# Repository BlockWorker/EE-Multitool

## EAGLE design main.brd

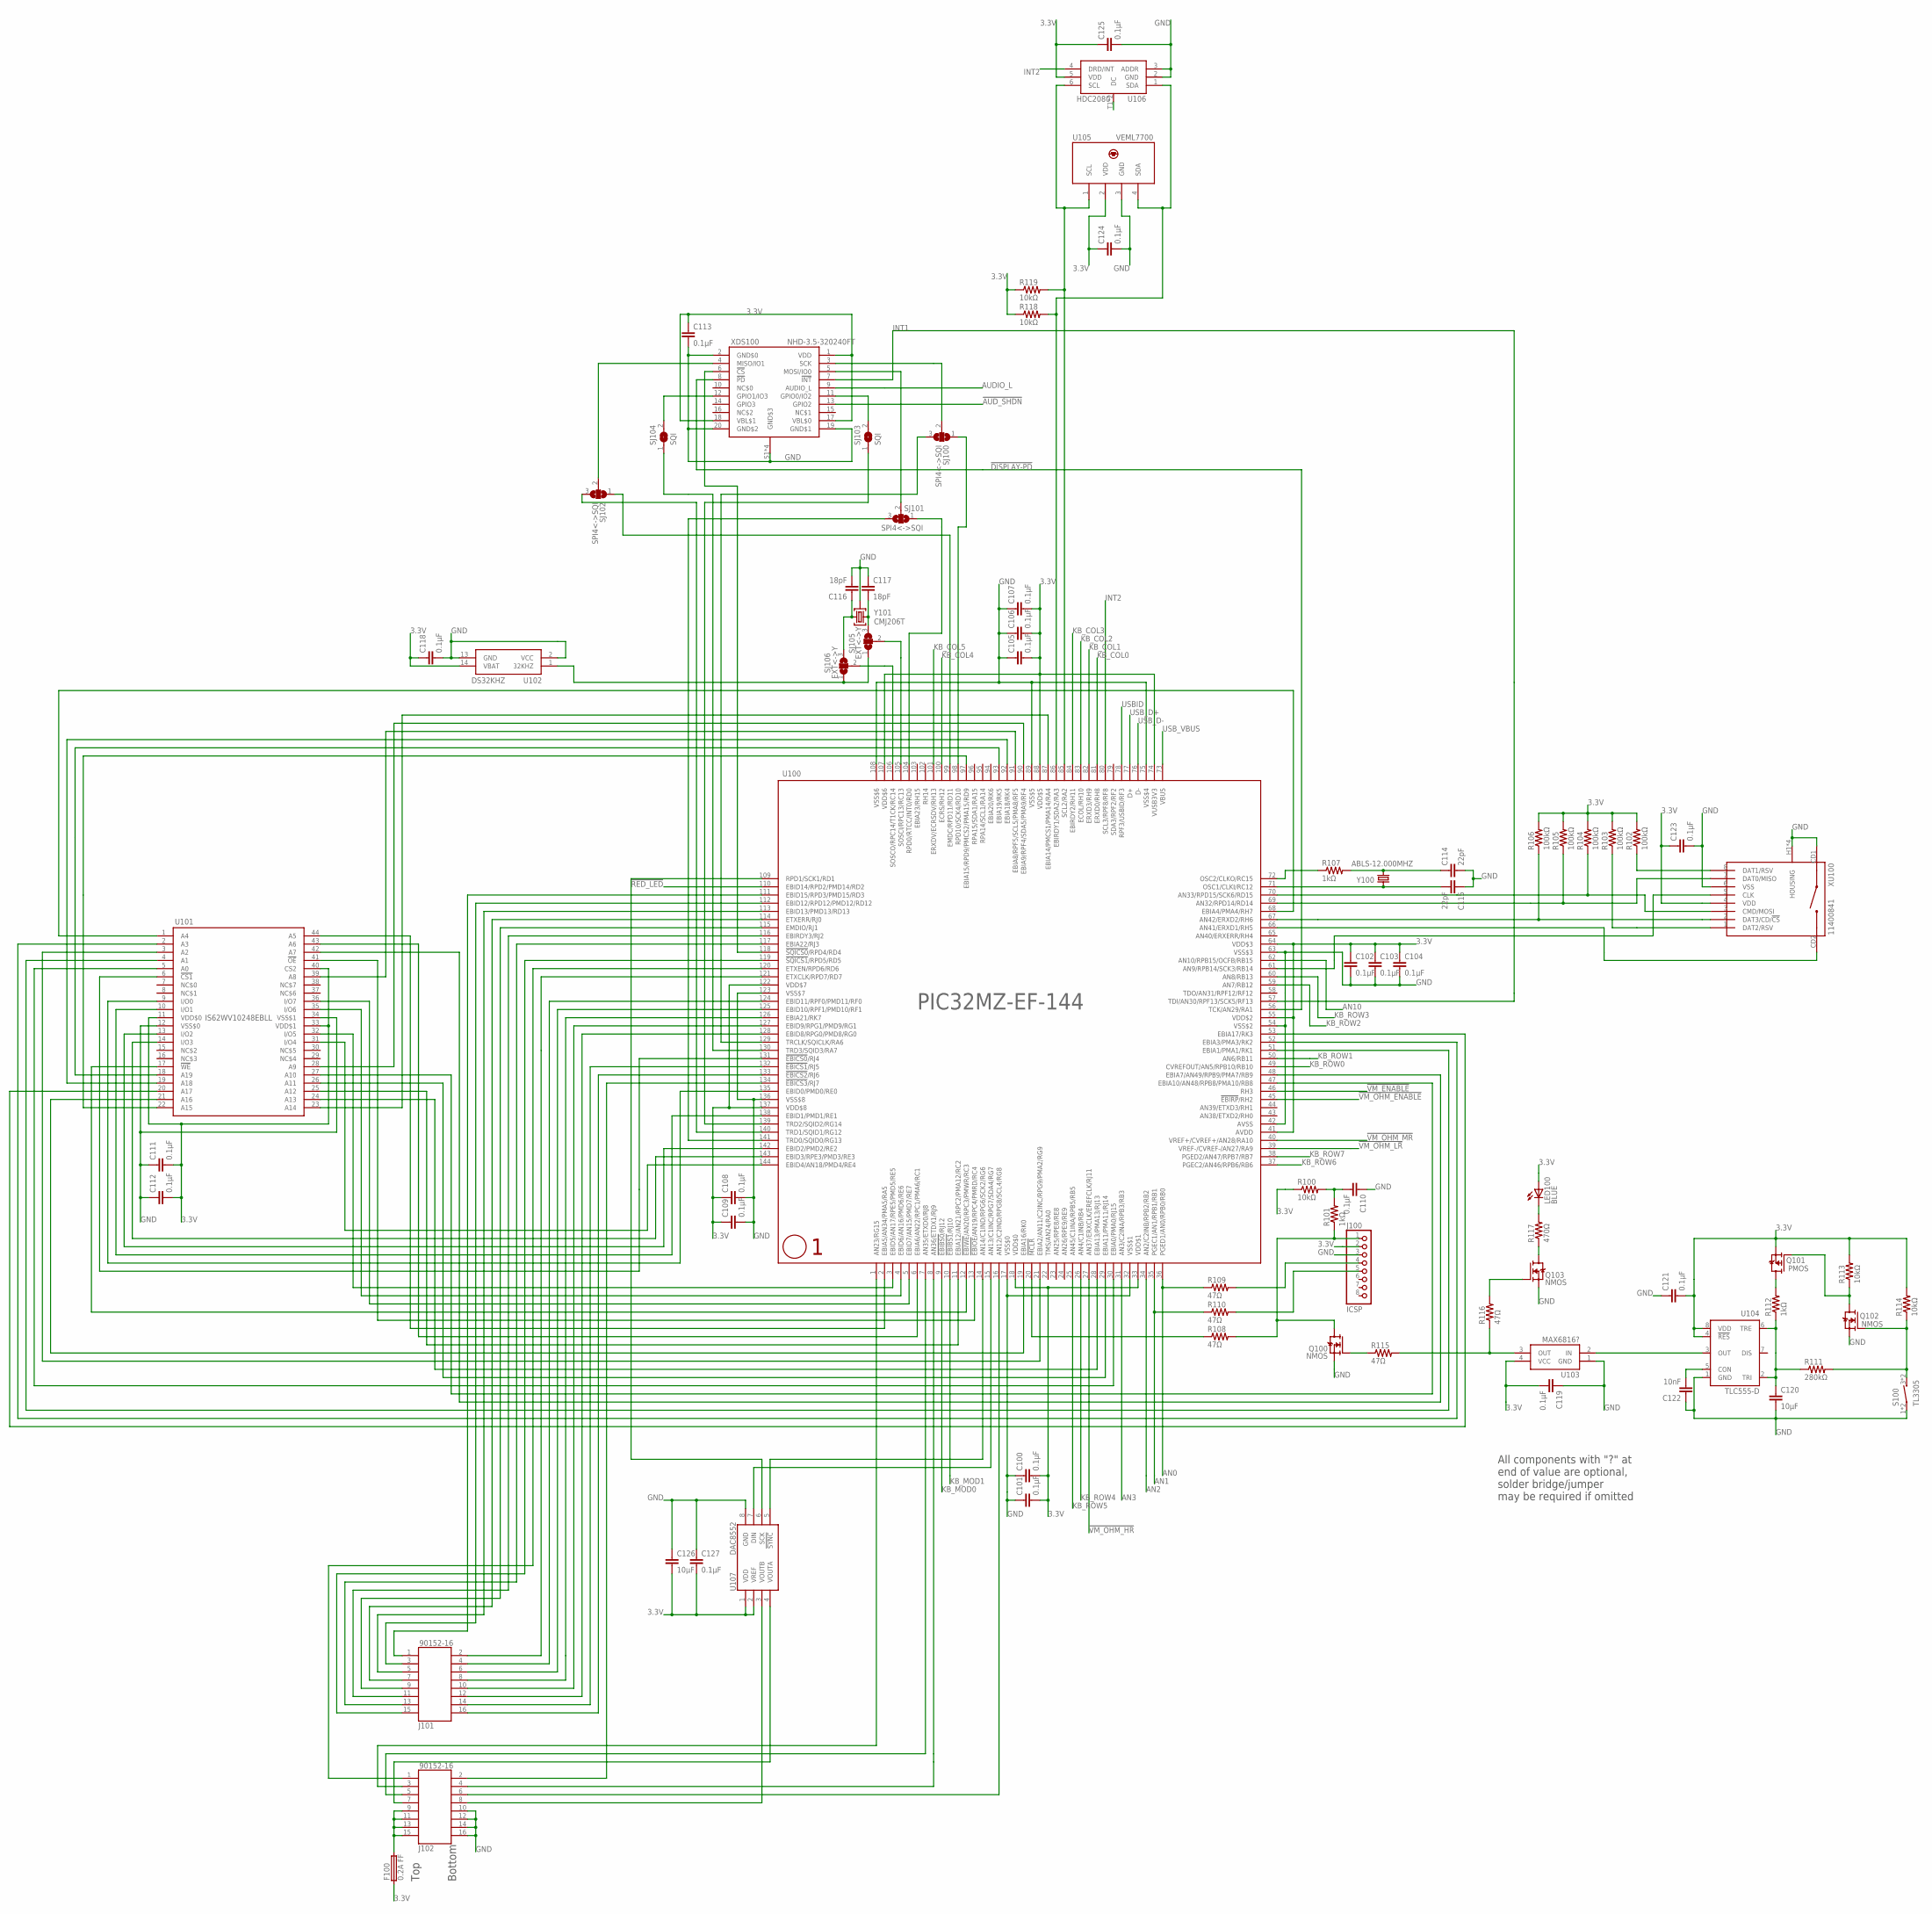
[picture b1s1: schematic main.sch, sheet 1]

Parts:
C100, C101, C102, C103, C104, C105, C106, C107, C108, C109, C110, C111, C112, C113, C118, C119, C121, C123, C124, C125, C127: 0.1µF; C0805K
C114, C115: 22pF; C0805K
C116, C117: 18pF; C0805K
C120, C126: 10µF; C0805K
C122: 10nF; C0805K
F100: 0.2A FF; C1206K
J100: ICSP; 1X08
J101, J102: 90152-16
LED100: BLUE; CHIP-LED0805
Q100, Q102, Q103: NMOS; SOT23
Q101: PMOS; SOT23
R100, R113, R114, R118, R119: 10kΩ; R0805
R101, R107, R112: 1kΩ; R0805
R102, R103, R104, R105, R106: 100kΩ; R0805
R108, R109, R110, R115, R116: 47Ω; R0805
R111: 280kΩ; R0805
R117: 470Ω; R0805
S100: TL3305; TL3305_MICROSWITCH
SJ100, SJ101, SJ102: SPI4<->SQI; SJ_2
SJ103, SJ104: SQI; SJ
SJ105, SJ106: EXT<->Y; SJ_2
U100: PIC32MZ-EF-144; LQFP144-20X20
U101: IS62WV10248EBLL; TSOP44
U102: DS32KHZ; SO16L
U103: MAX6816?; SOT143
U104: TLC555-D; SOIC8
U105: VEML7700
U106: HDC2080; PWSON-6
U107: DAC8552; MSOP8
XDS100: NHD-3.5-320240FT; NHD_DISPLAY_CONN
XU100: 11400841
Y100: ABLS-12.000MHZ; HC49US
Y101: CMJ206T; CMJ206T-CUSTOM

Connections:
3.3V: C100.2, C101.2, C102.1, C103.1, C104.1, C105.2, C106.2, C107.2, C108.1, C109.1, C111.2, C112.2, C113.1, C118.1, C119.2, C121.2, C123.1, C124.1, C125.1, C126.2, C127.2, F100.1, J100.2, LED100.A, Q101.2 (S), R100.1, R102.2, R103.2, R104.2, R105.2, R106.2, R113.2, R114.2, R118.1, R119.1, U100.18 (VDD$0), U100.33 (VDD$1), U100.41 (AVDD), U100.55 (VDD$2), U100.64 (VDD$3), U100.74 (VUSB3V3), U100.88 (VDD$5), U100.107 (VDD$6), U100.122 (VDD$7), U100.137 (VDD$8), U101.11 (VDD$0), U101.33 (VDD$1), U101.40 (CS2), U102.14 (VBAT), U103.4 (VCC), U104.4 (!RES), U104.8 (VDD), U105.2 (VDD), U106.5 (VDD), U107.1 (VDD), U107.2 (VREF), XDS100.1 (VDD), XDS100.17 (VBL$0), XDS100.18 (VBL$1), XU100.4 (VDD); also elsewhere on the board
!AUD_SHDN: XDS100.13 (GPIO2); also elsewhere on the board
!DISPLAY-PD: U100.56 (TCK/AN29/RA1), XDS100.8 (!PD)
!EBICS0: U100.131 (!EBICS0!/RJ4), U101.6 (!CS1)
!EBIOE: U100.13 (!EBIOE!/AN19/RPC4/PMRD/RC4), U101.41 (!OE)
!EBIWE: U100.12 (!EBIWE!/AN20/RPC3/PMWR/RC3), U101.17 (!WE)
!MCLR: R108.1, U100.20 (!MCLR)
!MCLR!_FILTER: C110.2, R100.2, R101.2
!MCLR!_R: J100.1, Q100.3 (D), R101.1, R108.2
!RED_LED: U100.110 (EBID14/RPD2/PMD14/RD2); also elsewhere on the board
!RESET_MAN!_RAW: Q102.1 (G), R111.2, R114.1, S100.3 (2), S100.4 (2)
!SQICS0: U100.118 (!SQICS0!/RPD4/RD4), XDS100.6 (!CS)
!VM_ENABLE: U100.46 (RH3); also elsewhere on the board
!VM_OHM_ENABLE: U100.45 (!EBIRP!/RH2); also elsewhere on the board
!VM_OHM_HR: U100.27 (AN37/ERXCLK/EREFCLK/RJ11); also elsewhere on the board
!VM_OHM_LR: U100.39 (VREF-/CVREF-/AN27/RA9); also elsewhere on the board
!VM_OHM_MR: U100.40 (VREF+/CVREF+/AN28/RA10); also elsewhere on the board
AN0: R109.1, U100.36 (PGED1/AN0/RPB0/RB0); also elsewhere on the board
AN1: R110.1, U100.35 (PGEC1/AN1/RPB1/RB1); also elsewhere on the board
AN2: U100.34 (AN2/C2INB/RPB2/RB2); also elsewhere on the board
AN3: U100.31 (AN3/C2INA/RPB3/RB3); also elsewhere on the board
AN10: U100.62 (AN10/RPB15/OCFB/RB15); also elsewhere on the board
AN12/A3: J102.6, U100.16 (AN12/C2IND/RPG8/SCL4/RG8)
AN23/A0: J102.3, U100.1 (AN23/RG15)
AN35/A1: J102.5, U100.7 (AN35/ETXD0/RJ8)
AN36/A2: J102.4, U100.8 (AN36/ETDX1/RJ9)
AUDIO_L: XDS100.9 (AUDIO_L); also elsewhere on the board
DAC_OUT_A: J102.7, U107.4 (VOUTA)
DAC_OUT_B: J102.8, U107.3 (VOUTB)
DISP_IO0: SJ101.2, XDS100.5 (MOSI/IO0)
DISP_IO1: SJ102.2, XDS100.4 (MISO/IO1)
DISP_IO2: SJ103.2, XDS100.11 (GPIO0/IO2)
DISP_IO3: SJ104.2, XDS100.12 (GPIO1/IO3)
DISP_SCK: SJ100.2, XDS100.3 (SCK)
EBIA0: U100.30 (EBIA0/PMA0/RJ15), U101.5 (A0)
EBIA1: U100.51 (EBIA1/PMA1/RK1), U101.4 (A1)
EBIA2: U100.21 (EBIA2/AN11/C2INC/RPG9/PMA2/RG9), U101.3 (A2)
EBIA3: U100.52 (EBIA3/PMA3/RK2), U101.2 (A3)
EBIA4: U100.68 (EBIA4/PMA4/RH7), U101.1 (A4)
EBIA5: U100.2 (EBIA5/AN34/PMA5/RA5), U101.44 (A5)
EBIA6: U100.6 (EBIA6/AN22/RPC1/PMA6/RC1), U101.43 (A6)
EBIA7: U100.48 (EBIA7/AN49/RPB9/PMA7/RB9), U101.42 (A7)
EBIA8: U100.91 (EBIA8/RPF5/SCL5/PMA8/RF5), U101.39 (A8)
EBIA9: U100.90 (EBIA9/RPF4/SDA5/PMA9/RF4), U101.28 (A9)
EBIA10: U100.47 (EBIA10/AN48/RPB8/PMA10/RB8), U101.27 (A10)
EBIA11: U100.29 (EBIA11/PMA11/RJ14), U101.26 (A11)
EBIA12: U100.11 (EBIA12/AN21/RPC2/PMA12/RC2), U101.25 (A12)
EBIA13: U100.28 (EBIA13/PMA13/RJ13), U101.24 (A13)
EBIA14: U100.87 (EBIA14/PMCS1/PMA14/RA4), U101.23 (A14)
EBIA15: U100.97 (EBIA15/RPD9/PMCS2/PMA15/RD9), U101.22 (A15)
EBIA16: U100.19 (EBIA16/RK0), U101.21 (A16)
EBIA17: U100.53 (EBIA17/RK3), U101.20 (A17)
EBIA18: U100.92 (EBIA18/RK4), U101.19 (A18)
EBIA19: U100.93 (EBIA19/RK5), U101.18 (A19)
EBID0: U100.135 (EBID0/PMD0/RE0), U101.9 (I/O0)
EBID1: U100.138 (EBID1/PMD1/RE1), U101.10 (I/O1)
EBID2: U100.142 (EBID2/PMD2/RE2), U101.13 (I/O2)
EBID3: U100.143 (EBID3/RPE3/PMD3/RE3), U101.14 (I/O3)
EBID4: U100.144 (EBID4/AN18/PMD4/RE4), U101.31 (I/O4)
EBID5: U100.3 (EBID5/AN17/RPE5/PMD5/RE5), U101.32 (I/O5)
EBID6: U100.4 (EBID6/AN16/PMD6/RE6), U101.35 (I/O6)
EBID7: U100.5 (EBID7/AN15/PMD7/RE7), U101.36 (I/O7)
GND: C100.1, C101.1, C102.2, C103.2, C104.2, C105.1, C106.1, C107.1, C108.2, C109.2, C110.1, C111.1, C112.1, C113.2, C114.2, C115.1, C116.2, C117.1, C118.2, C119.1, C120.2, C121.1, C122.1, C123.2, C124.2, C125.2, C126.1, C127.1, J100.3, J102.10, J102.12, J102.14, J102.16, Q100.2 (S), Q102.2 (S), Q103.2 (S), S100.1, S100.2 (1), U100.17 (VSS$0), U100.32 (VSS$1), U100.42 (AVSS), U100.54 (VSS$2), U100.63 (VSS$3), U100.75 (VSS$4), U100.89 (VSS$5), U100.108 (VSS$6), U100.123 (VSS$7), U100.136 (VSS$8), U101.12 (VSS$0), U101.34 (VSS$1), U102.2 (VCC), U102.13 (GND), U103.1 (GND), U104.1 (GND), U105.3 (GND), U106.2 (GND), U106.3 (ADDR), U107.8 (GND), XDS100.2 (GND$0), XDS100.19 (GND$1), XDS100.20 (GND$2), XDS100.S1 (GND$3), XDS100.S2 (GND$3), XDS100.S3 (GND$3), XDS100.S4 (GND$3), XU100.6 (VSS), XU100.CD1, XU100.H1 (HOUSING), XU100.H2 (HOUSING), XU100.H3 (HOUSING), XU100.H4 (HOUSING), Y101.GND (3); also elsewhere on the board
INT1: U100.57 (TDI/AN30/RPF13/SCK5/RF13), XDS100.7 (!INT)
INT2: U100.80 (SCL3/RPF8/RF8), U106.4 (DRD/INT)
KB_COL0: U100.81 (ERXD0/RH8); also elsewhere on the board
KB_COL1: U100.82 (ERXD3/RH9); also elsewhere on the board
KB_COL2: U100.83 (ECOL/RH10); also elsewhere on the board
KB_COL3: U100.84 (EBIRDY2/RH11); also elsewhere on the board
KB_COL4: U100.100 (ECRS/RH12); also elsewhere on the board
KB_COL5: U100.101 (ERXDV/ECRSDV/RH13); also elsewhere on the board
KB_MOD0: U100.9 (!EBIBS0!/RJ12); also elsewhere on the board
KB_MOD1: U100.10 (!EBIBS1!/RJ10); also elsewhere on the board
KB_ROW0: U100.49 (CVREFOUT/AN5/RPB10/RB10); also elsewhere on the board
KB_ROW1: U100.50 (AN6/RB11); also elsewhere on the board
KB_ROW2: U100.59 (AN7/RB12); also elsewhere on the board
KB_ROW3: U100.60 (AN8/RB13); also elsewhere on the board
KB_ROW4: U100.26 (AN4/C1INB/RB4); also elsewhere on the board
KB_ROW5: U100.25 (AN45/C1INA/RPB5/RB5); also elsewhere on the board
KB_ROW6: U100.37 (PGEC2/AN46/RPB6/RB6); also elsewhere on the board
KB_ROW7: U100.38 (PGED2/AN47/RPB7/RB7); also elsewhere on the board
LED100_K: LED100.C, R117.2
LED100_SWITCHED: Q103.3 (D), R117.1
OSC1: C115.2, U100.71 (OSC1/CLKI/RC12), Y100.1
OSC2: R107.1, U100.72 (OSC2/CLKO/RC15)
OSC2_R: C114.1, R107.2, Y100.2
OUT_3.3V: F100.2, J102.9, J102.11, J102.13, J102.15
PGEC_R: J100.5, R110.2
PGED_R: J100.4, R109.2
RD3/D0: J101.1, U100.111 (EBID15/RPD3/PMD15/RD3)
RD5/D7: J101.15, U100.119 (!SQICS1!/RPD5/RD5)
RD6/D8: J102.1, U100.120 (ETXEN/RPD6/RD6)
RD7/D9: J101.2, U100.121 (ETXCLK/RPD7/RD7)
RD12/D1: J101.3, U100.112 (EBID12/RPD12/PMD12/RD12)
RD13/D2: J101.5, U100.113 (EBID13/PMD13/RD13)
RESET_MAN_CAP: C120.1, R111.1, R112.1, U104.2 (TRI), U104.6 (TRE)
RESET_MAN_CHG: Q101.3 (D), R112.2
RESET_MAN_CON: C122.2, U104.5 (CON)
RESET_MAN_FINAL: R115.2, R116.1, U103.3 (OUT)
RESET_MAN_GATE: Q100.1 (G), R115.1
RESET_MAN_LED_GATE: Q103.1 (G), R116.2
RESET_MAN_RAW: Q101.1 (G), Q102.3 (D), R113.1
RESET_MAN_TIMED: U103.2 (IN), U104.3 (OUT)
RF0/D10: J101.4, U100.124 (EBID11/RPF0/PMD11/RF0)
RF1/D11: J101.6, U100.125 (EBID10/RPF1/PMD10/RF1)
RG0/D14: J101.12, U100.128 (EBID8/RPG0/PMD8/RG0)
RG1/D13: J101.10, U100.127 (EBID9/RPG1/PMD9/RG1)
RJ0/D3: J101.7, U100.114 (ETXERR/RJ0)
RJ1/D4: J101.9, U100.115 (EMDIO/RJ1)
RJ2/D5: J101.11, U100.116 (EBIRDY3/RJ2)
RJ3/D6: J101.13, U100.117 (EBIA22/RJ3)
RJ5/D15: J101.14, U100.132 (!EBICS1!/RJ5)
RJ6/D16: J101.16, U100.133 (!EBICS2!/RJ6)
RJ7/D17: J102.2, U100.134 (!EBICS3!/RJ7)
RK7/D12: J101.8, U100.126 (EBIA21/RK7)
SCK1: U100.109 (RPD1/SCK1/RD1), U107.6 (SCK)
SCK3: U100.61 (AN9/RPB14/SCK3/RB14), XU100.5 (CLK)
SCK4: SJ100.1, U100.98 (RPD10/SCK4/RD10)
SCL2: R119.2, U100.85 (SCL2/RA2), U105.1 (SCL), U106.6 (SCL)
SDA2: R118.2, U100.86 (EBIRDY1/SDA2/RA3), U105.4 (SDA), U106.1 (SDA)
SDI3: R105.1, U100.69 (AN32/RPD14/RD14), XU100.7 (DAT0/MISO)
SDI4: SJ102.1, U100.99 (EMDC/RPD11/RD11)
SDO1: U100.15 (AN13/C1INC/RPG7/SDA4/RG7), U107.7 (DIN)
SDO3: R104.1, U100.70 (AN33/RPD15/SCK6/RD15), XU100.3 (CMD/MOSI)
SDO4: SJ101.1, U100.104 (RPD0/RTCC/INT0/RD0)
SD_CS: R106.1, U100.67 (AN42/ERXD2/RH6), XU100.2 (DAT3/CD/!CS)
SD_DETECT: U100.66 (AN41/ERXD1/RH5), XU100.CD2
SD_RSV1: R102.1, XU100.8 (DAT1/RSV)
SD_RSV2: R103.1, XU100.1 (DAT2/RSV)
SOSCI: SJ105.2, U100.105 (SOSCI/RPC13/RC13)
SOSCO: SJ106.2, U100.106 (SOSCO/RPC14/T1CK/RC14)
SOSC_1: C117.2, SJ105.3, Y101.2
SOSC_2: C116.1, SJ106.3, Y101.1
SOSC_EXT: SJ105.1, SJ106.1, U102.1 (32KHZ)
SQICLK: SJ100.3, U100.129 (TRCLK/SQICLK/RA6)
SQID0: SJ101.3, U100.141 (TRD0/SQID0/RG13)
SQID1: SJ102.3, U100.140 (TRD1/SQID1/RG12)
SQID2: SJ103.1, U100.139 (TRD2/SQID2/RG14)
SQID3: SJ104.1, U100.130 (TRD3/SQID3/RA7)
SS1: U100.14 (AN14/C1IND/RPG6/SCK2/RG6), U107.5 (!SYNC)
U106_TP: U106.T1 (DC), U106.T2 (DC)
USBID: U100.78 (RPF3/USBID/RF3); also elsewhere on the board
USB_D+: U100.77 (D+); also elsewhere on the board
USB_D-: U100.76 (D-); also elsewhere on the board
USB_VBUS: U100.73 (VBUS); also elsewhere on the board

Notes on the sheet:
All components with "?" at end of value are optional, solder bridge/jumper may be required if omitted
Top Bottom

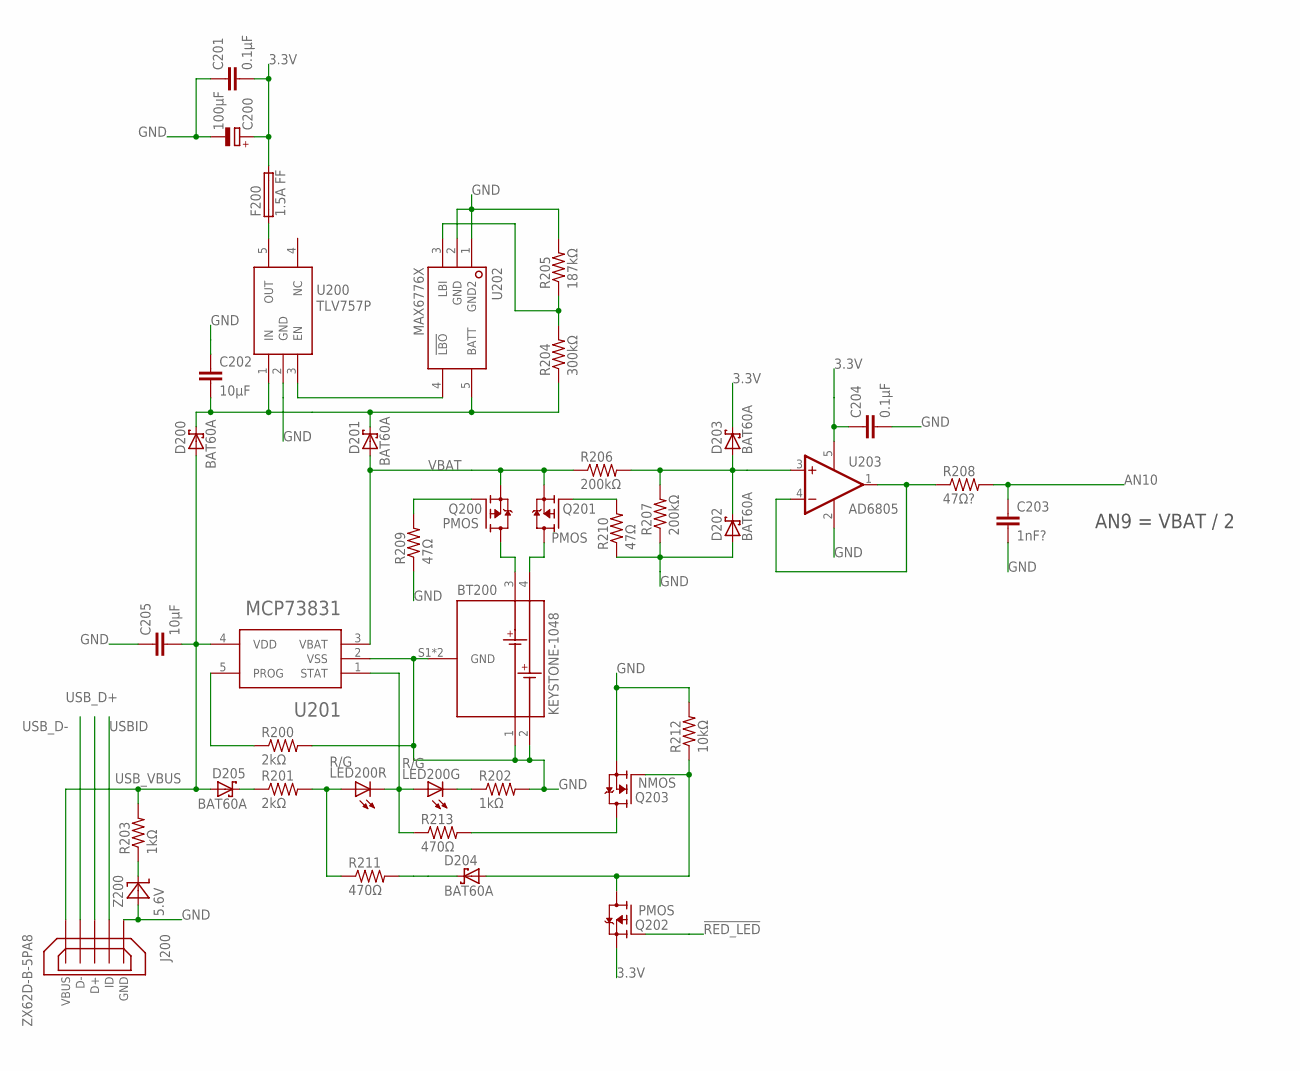
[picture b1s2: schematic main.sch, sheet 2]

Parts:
BT200: KEYSTONE-1048
C200: 100µF; C1206K-POL
C201, C204: 0.1µF; C0805K
C202, C205: 10µF; C0805K
C203: 1nF?; C0805K
D200, D201, D202, D203, D204, D205: BAT60A; SOD323
F200: 1.5A FF; C0805K
J200: ZX62D-B-5PA8
LED200: R/G; 0805-DUALLED
Q200, Q201, Q202: PMOS; SOT23
Q203: NMOS; SOT23
R200, R201: 2kΩ; R0805
R202, R203: 1kΩ; R0805
R204: 300kΩ; R0805
R205: 187kΩ; R0805
R206, R207: 200kΩ; R0805
R208: 47Ω?; R0805
R209, R210: 47Ω; R0805
R211, R213: 470Ω; R0805
R212: 10kΩ; R0805
U200: TLV757P; SOT23-5L
U201: MCP73831; SOT23-5L
U202: MAX6776X; SC70-5
U203: AD6805; SOT23-5L
Z200: 5.6V; SOD323HE

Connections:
3.3V: C200.1 (+), C201.2, C204.1, D203.1 (C), F200.2, Q202.2 (S), U203.5 (V+); also elsewhere on the board
!RED_LED: Q202.1 (G); also elsewhere on the board
AN10: C203.1, R208.2; also elsewhere on the board
BAT1_PMOS_GATE: Q200.1 (G), R209.2
BAT2_PMOS_GATE: Q201.1 (G), R210.2
BATM_LBI: R204.2, R205.1, U202.3 (LBI)
CHG_PROG: R200.1, U201.5 (PROG)
CHG_STAT: LED200.A2 (A), LED200.K1 (C), R213.1, U201.1 (STAT)
GND: BT200.1 (BAT1-), BT200.2 (BAT2-), BT200.S1 (GND), BT200.S2 (GND), C200.2 (-), C201.1, C202.1, C203.2, C204.2, C205.1, D202.2 (A), J200.5 (GND), J200.S1 (GND), J200.S2 (GND), J200.S3 (GND), J200.S4 (GND), Q203.2 (S), R200.2, R202.2, R205.2, R207.1, R209.1, R210.1, R212.2, U200.2 (GND), U201.2 (VSS), U202.1 (GND2), U202.2 (GND), U203.2 (V-), Z200.2 (A); also elsewhere on the board
LED200_GK: LED200.K2 (C), R202.1
LED200_RA: LED200.A1 (A), R201.2, R211.1
LED200_RA_EXT: D204.1 (C), R211.2
LED200_RA_INT: D205.1 (C), R201.1
LED200_RK_EXT: Q203.3 (D), R213.2
RED_LED: D204.2 (A), Q202.3 (D), Q203.1 (G), R212.1
USBID: J200.4 (ID); also elsewhere on the board
USB_D+: J200.3 (D+); also elsewhere on the board
USB_D-: J200.2 (D-); also elsewhere on the board
USB_VBUS: C205.2, D200.2 (A), D205.2 (A), J200.1 (VBUS), R203.2, U201.4 (VDD); also elsewhere on the board
VBAT: D201.2 (A), Q200.2 (S), Q201.2 (S), R206.1, U201.3 (VBAT)
VBAT1: BT200.3 (BAT1+), Q200.3 (D)
VBAT2: BT200.4 (BAT2+), Q201.3 (D)
VBAT_SENSE: D202.1 (C), D203.2 (A), R206.2, R207.2, U203.3 (+IN)
VBAT_SENSE_BUF: R208.1, U203.1 (OUT), U203.4 (-IN)
VREG_EN: U200.3 (EN), U202.4 (!LBO)
VREG_IN: C202.2, D200.1 (C), D201.1 (C), R204.1, U200.1 (IN), U202.5 (BATT)
VREG_OUT: F200.1, U200.5 (OUT)
Z200_K: R203.1, Z200.1 (C)

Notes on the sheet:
AN9 = VBAT / 2

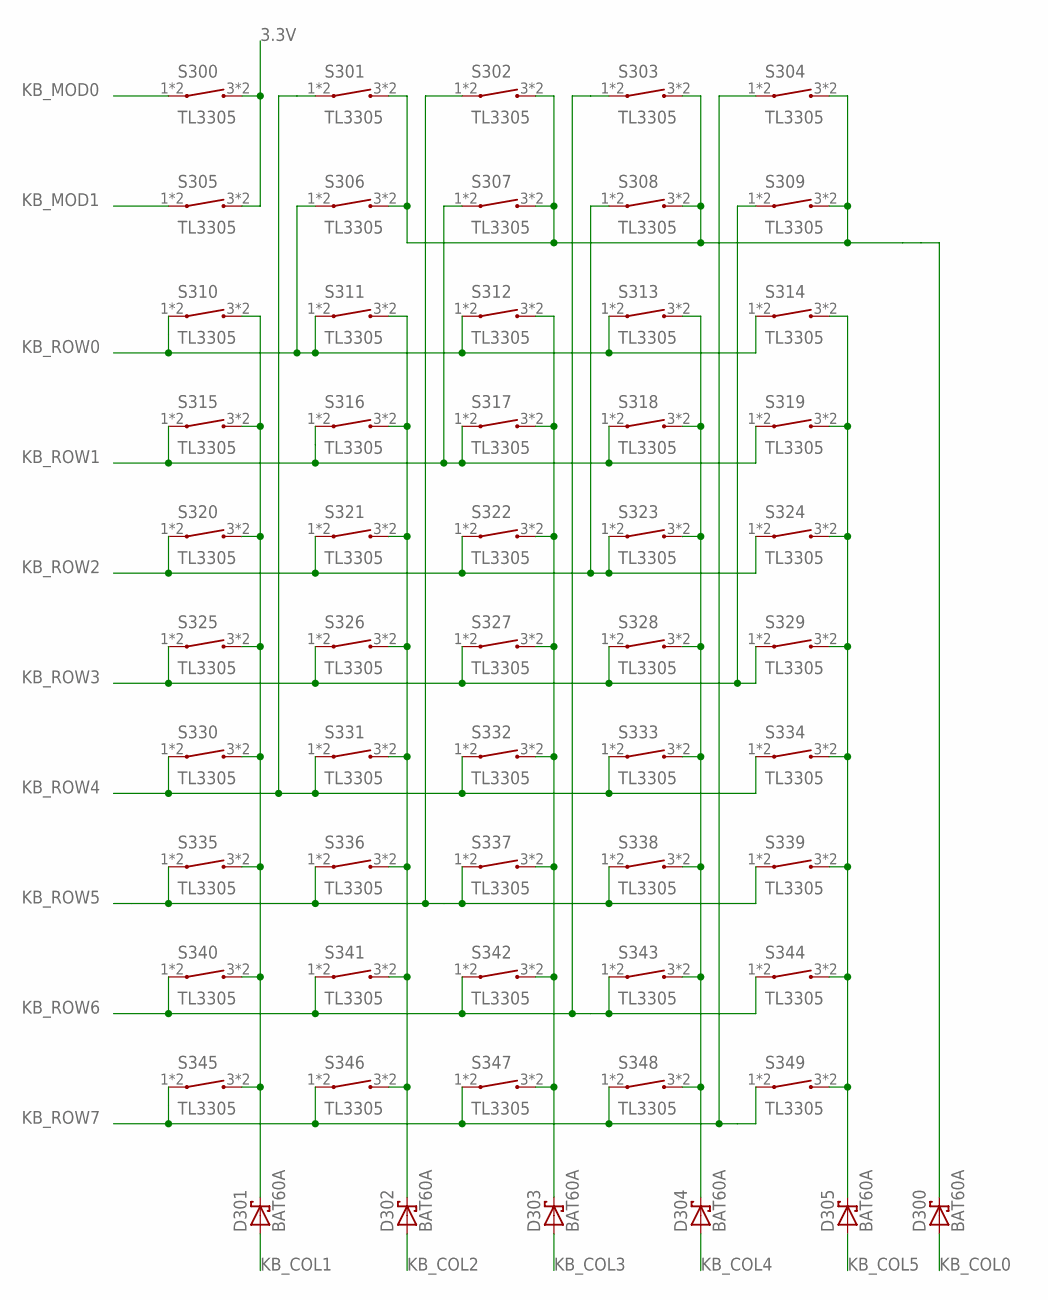
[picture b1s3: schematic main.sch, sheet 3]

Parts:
D300, D301, D302, D303, D304, D305: BAT60A; SOD323
S300, S301, S302, S303, S304, S305, S306, S307, S308, S309, S310, S311, S312, S313, S314, S315, S316, S317, S318, S319, S320, S321, S322, S323, S324, S325, S326, S327, S328, S329, S330, S331, S332, S333, S334, S335, S336, S337, S338, S339, S340, S341, S342, S343, S344, S345, S346, S347, S348, S349: TL3305; TL3305_MICROSWITCH

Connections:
3.3V: S300.3 (2), S300.4 (2), S305.3 (2), S305.4 (2); also elsewhere on the board
KB_COL0: D300.2 (A); also elsewhere on the board
KB_COL0_F: D300.1 (C), S301.3 (2), S301.4 (2), S302.3 (2), S302.4 (2), S303.3 (2), S303.4 (2), S304.3 (2), S304.4 (2), S306.3 (2), S306.4 (2), S307.3 (2), S307.4 (2), S308.3 (2), S308.4 (2), S309.3 (2), S309.4 (2)
KB_COL1: D301.2 (A); also elsewhere on the board
KB_COL1_F: D301.1 (C), S310.3 (2), S310.4 (2), S315.3 (2), S315.4 (2), S320.3 (2), S320.4 (2), S325.3 (2), S325.4 (2), S330.3 (2), S330.4 (2), S335.3 (2), S335.4 (2), S340.3 (2), S340.4 (2), S345.3 (2), S345.4 (2)
KB_COL2: D302.2 (A); also elsewhere on the board
KB_COL2_F: D302.1 (C), S311.3 (2), S311.4 (2), S316.3 (2), S316.4 (2), S321.3 (2), S321.4 (2), S326.3 (2), S326.4 (2), S331.3 (2), S331.4 (2), S336.3 (2), S336.4 (2), S341.3 (2), S341.4 (2), S346.3 (2), S346.4 (2)
KB_COL3: D303.2 (A); also elsewhere on the board
KB_COL3_F: D303.1 (C), S312.3 (2), S312.4 (2), S317.3 (2), S317.4 (2), S322.3 (2), S322.4 (2), S327.3 (2), S327.4 (2), S332.3 (2), S332.4 (2), S337.3 (2), S337.4 (2), S342.3 (2), S342.4 (2), S347.3 (2), S347.4 (2)
KB_COL4: D304.2 (A); also elsewhere on the board
KB_COL4_F: D304.1 (C), S313.3 (2), S313.4 (2), S318.3 (2), S318.4 (2), S323.3 (2), S323.4 (2), S328.3 (2), S328.4 (2), S333.3 (2), S333.4 (2), S338.3 (2), S338.4 (2), S343.3 (2), S343.4 (2), S348.3 (2), S348.4 (2)
KB_COL5: D305.2 (A); also elsewhere on the board
KB_COL5_F: D305.1 (C), S314.3 (2), S314.4 (2), S319.3 (2), S319.4 (2), S324.3 (2), S324.4 (2), S329.3 (2), S329.4 (2), S334.3 (2), S334.4 (2), S339.3 (2), S339.4 (2), S344.3 (2), S344.4 (2), S349.3 (2), S349.4 (2)
KB_MOD0: S300.1, S300.2 (1); also elsewhere on the board
KB_MOD1: S305.1, S305.2 (1); also elsewhere on the board
KB_ROW0: S306.1, S306.2 (1), S310.1, S310.2 (1), S311.1, S311.2 (1), S312.1, S312.2 (1), S313.1, S313.2 (1), S314.1, S314.2 (1); also elsewhere on the board
KB_ROW1: S307.1, S307.2 (1), S315.1, S315.2 (1), S316.1, S316.2 (1), S317.1, S317.2 (1), S318.1, S318.2 (1), S319.1, S319.2 (1); also elsewhere on the board
KB_ROW2: S308.1, S308.2 (1), S320.1, S320.2 (1), S321.1, S321.2 (1), S322.1, S322.2 (1), S323.1, S323.2 (1), S324.1, S324.2 (1); also elsewhere on the board
KB_ROW3: S309.1, S309.2 (1), S325.1, S325.2 (1), S326.1, S326.2 (1), S327.1, S327.2 (1), S328.1, S328.2 (1), S329.1, S329.2 (1); also elsewhere on the board
KB_ROW4: S301.1, S301.2 (1), S330.1, S330.2 (1), S331.1, S331.2 (1), S332.1, S332.2 (1), S333.1, S333.2 (1), S334.1, S334.2 (1); also elsewhere on the board
KB_ROW5: S302.1, S302.2 (1), S335.1, S335.2 (1), S336.1, S336.2 (1), S337.1, S337.2 (1), S338.1, S338.2 (1), S339.1, S339.2 (1); also elsewhere on the board
KB_ROW6: S303.1, S303.2 (1), S340.1, S340.2 (1), S341.1, S341.2 (1), S342.1, S342.2 (1), S343.1, S343.2 (1), S344.1, S344.2 (1); also elsewhere on the board
KB_ROW7: S304.1, S304.2 (1), S345.1, S345.2 (1), S346.1, S346.2 (1), S347.1, S347.2 (1), S348.1, S348.2 (1), S349.1, S349.2 (1); also elsewhere on the board

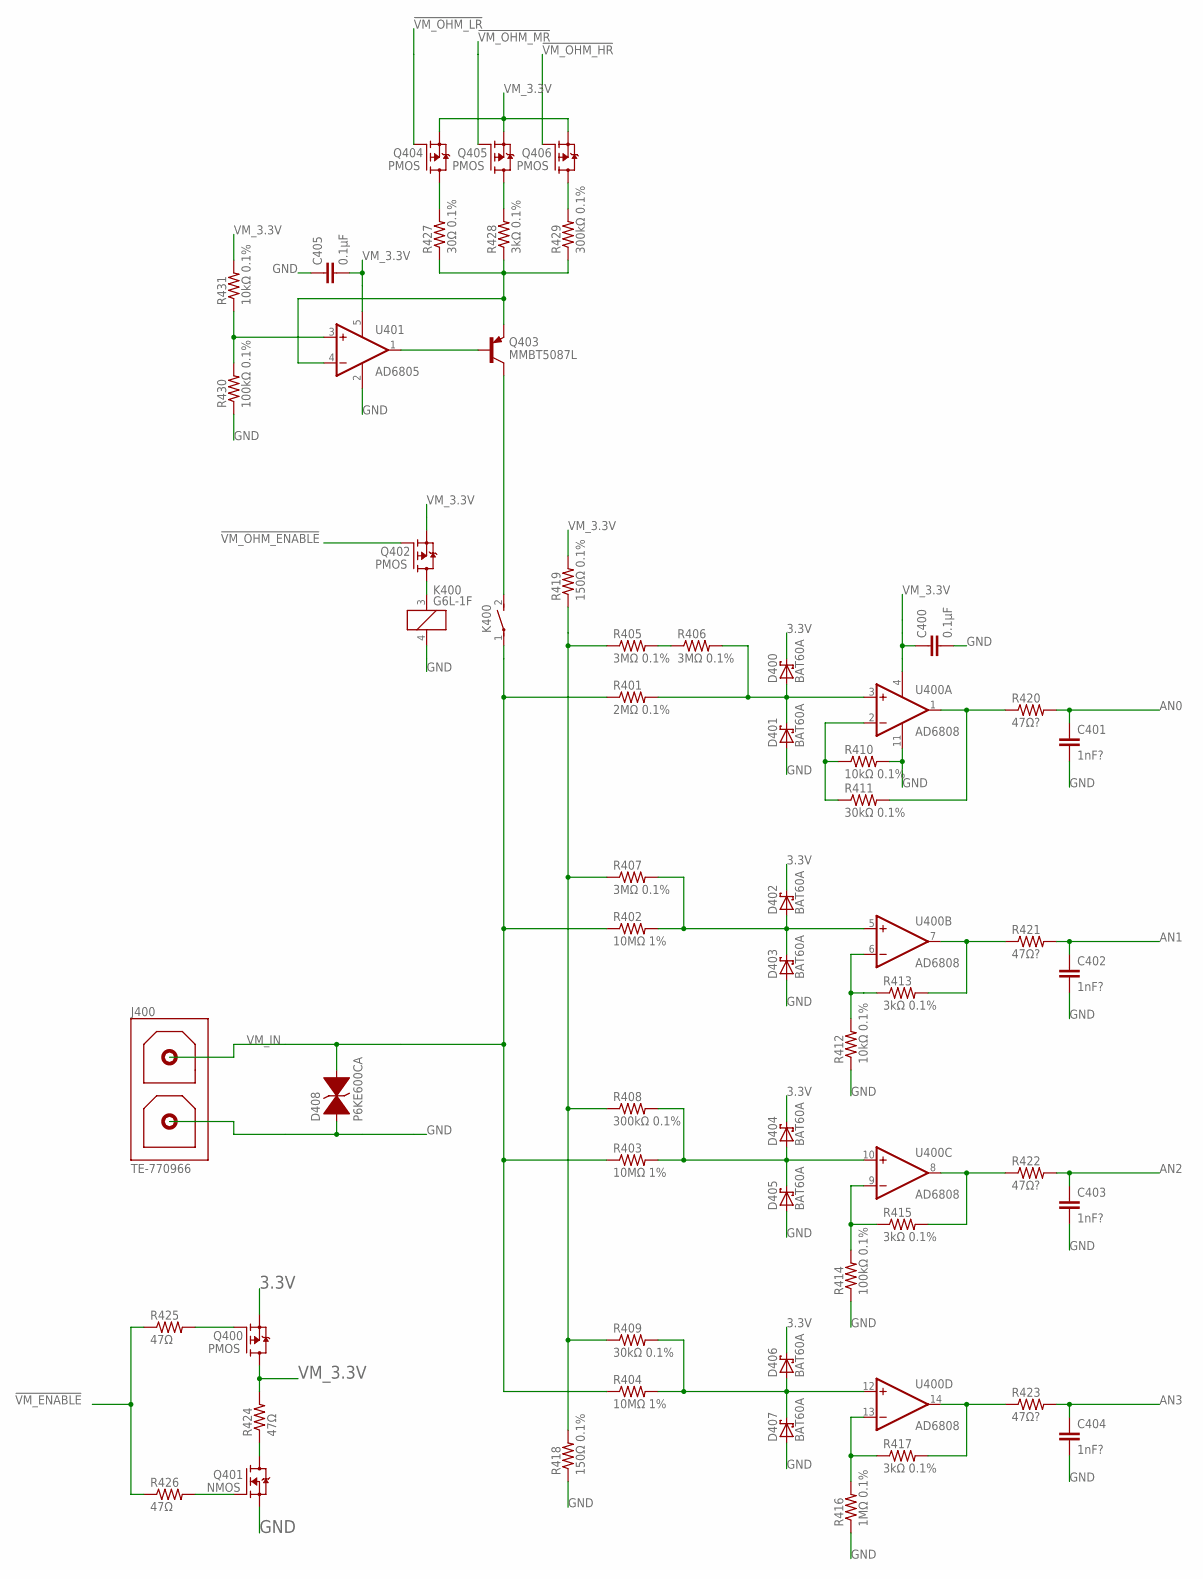
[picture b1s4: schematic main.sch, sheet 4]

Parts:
C400, C405: 0.1µF; C0805K
C401, C402, C403, C404: 1nF?; C0805K
D400, D401, D402, D403, D404, D405, D406, D407: BAT60A; SOD323
D408: P6KE600CA; DO-204AC
J400: TE-770966
K400: G6L-1F
Q400, Q402, Q404, Q405, Q406: PMOS; SOT23
Q401: NMOS; SOT23
Q403: MMBT5087L; SOT23
R401: 2MΩ 0.1%; R1206
R402, R403, R404: 10MΩ 1%; R1206
R405, R406, R407: 3MΩ 0.1%; R0805
R408, R429: 300kΩ 0.1%; R0805
R409, R411: 30kΩ 0.1%; R0805
R410, R412, R431: 10kΩ 0.1%; R0805
R413, R415, R417, R428: 3kΩ 0.1%; R0805
R414, R430: 100kΩ 0.1%; R0805
R416: 1MΩ 0.1%; R0805
R418, R419: 150Ω 0.1%; R0805
R420, R421, R422, R423: 47Ω?; R0805
R424, R425, R426: 47Ω; R0805
R427: 30Ω 0.1%; R0805
U400: AD6808; SO14
U401: AD6805; SOT23-5L

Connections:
3.3V: D400.1 (C), D402.1 (C), D404.1 (C), D406.1 (C), Q400.2 (S); also elsewhere on the board
!VM_ENABLE: R425.1, R426.1; also elsewhere on the board
!VM_OHM_ENABLE: Q402.1 (G); also elsewhere on the board
!VM_OHM_HR: Q406.1 (G); also elsewhere on the board
!VM_OHM_LR: Q404.1 (G); also elsewhere on the board
!VM_OHM_MR: Q405.1 (G); also elsewhere on the board
AN0: C401.1, R420.2; also elsewhere on the board
AN1: C402.1, R421.2; also elsewhere on the board
AN2: C403.1, R422.2; also elsewhere on the board
AN3: C404.1, R423.2; also elsewhere on the board
GND: C400.2, C401.2, C402.2, C403.2, C404.2, C405.1, D401.2 (A), D403.2 (A), D405.2 (A), D407.2 (A), D408.1, J400.1, K400.4 (2), Q401.2 (S), R410.2, R412.1, R414.1, R416.1, R418.1, R430.1, U400.11 (V-), U401.2 (V-); also elsewhere on the board
VM_0.5_IN: D400.2 (A), D401.1 (C), R401.2, R406.2, U400.3 (+IN)
VM_0.5_OUT: R411.2, R420.1, U400.1 (OUT)
VM_0.5_R: R405.2, R406.1
VM_0.5_RE: R410.1, R411.1, U400.2 (-IN)
VM_1.65V: R405.1, R407.1, R408.1, R409.1, R418.2, R419.1
VM_3.3V: C400.1, C405.2, Q400.3 (D), Q402.2 (S), Q404.2 (S), Q405.2 (S), Q406.2 (S), R419.2, R424.2, R431.2, U400.4 (V+), U401.5 (V+)
VM_3.3V_SHP: Q401.3 (D), R424.1
VM_5_IN: D402.2 (A), D403.1 (C), R402.2, R407.2, U400.5 (+IN)
VM_5_OUT: R413.2, R421.1, U400.7 (OUT)
VM_5_RE: R412.2, R413.1, U400.6 (-IN)
VM_50_IN: D404.2 (A), D405.1 (C), R403.2, R408.2, U400.10 (+IN)
VM_50_OUT: R415.2, R422.1, U400.8 (OUT)
VM_50_RE: R414.2, R415.1, U400.9 (-IN)
VM_500_IN: D406.2 (A), D407.1 (C), R404.2, R409.2, U400.12 (+IN)
VM_500_OUT: R417.2, R423.1, U400.14 (OUT)
VM_500_RE: R416.2, R417.1, U400.13 (-IN)
VM_IN: D408.2, J400.2, K400.1, R401.1, R402.1, R403.1, R404.1
VM_NMOS_GATE: Q401.1 (G), R426.2
VM_OHM_1U: Q406.3 (D), R429.2
VM_OHM_10M: Q404.3 (D), R427.2
VM_OHM_100U: Q405.3 (D), R428.2
VM_OHM_COIL: K400.3 (1), Q402.3 (D)
VM_OHM_CTRL: Q403.1 (B), U401.1 (OUT)
VM_OHM_ICT: Q403.2 (E), R427.1, R428.1, R429.1, U401.4 (-IN)
VM_OHM_IOUT: K400.2 (S), Q403.3 (C)
VM_OHM_VREF: R430.2, R431.1, U401.3 (+IN)
VM_PMOS_GATE: Q400.1 (G), R425.2

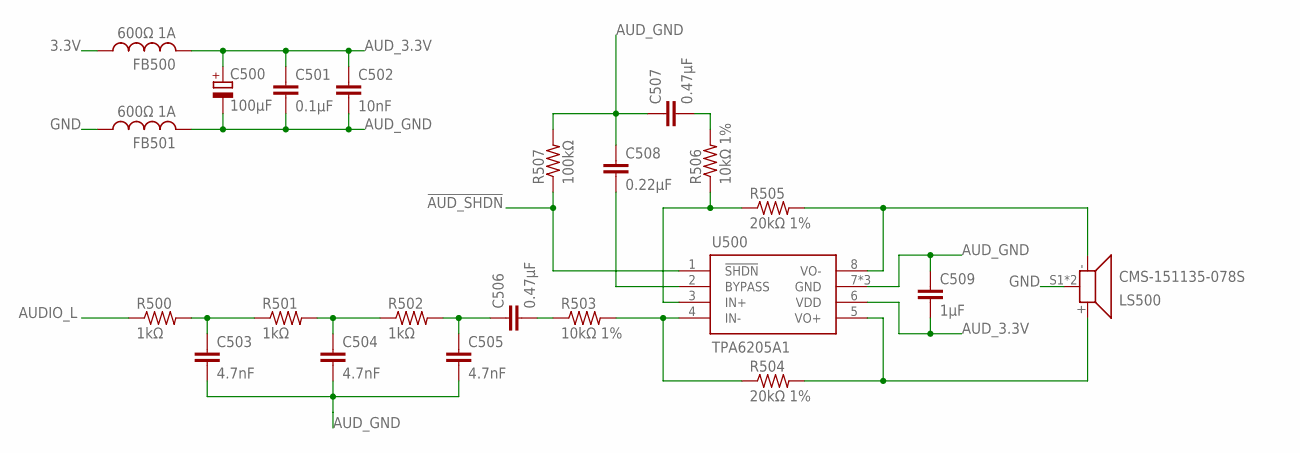
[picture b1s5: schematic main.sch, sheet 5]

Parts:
C500: 100µF; C1206K-POL
C501: 0.1µF; C0805K
C502: 10nF; C0805K
C503, C504, C505: 4.7nF; C0805K
C506, C507: 0.47µF; C0805K
C508: 0.22µF; C0805K
C509: 1µF; C0805K
FB500, FB501: 600Ω 1A; C0805K
LS500: CMS-151135-078S
R500, R501, R502: 1kΩ; R0805
R503, R506: 10kΩ 1%; R0805
R504, R505: 20kΩ 1%; R0805
R507: 100kΩ; R0805
U500: TPA6205A1; MSOP8-TP

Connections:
3.3V: FB500.1; also elsewhere on the board
!AUD_SHDN: R507.1, U500.1 (!SHDN); also elsewhere on the board
AUDIO_L: R500.1; also elsewhere on the board
AUD_3.3V: C500.1 (+), C501.1, C502.1, C509.2, FB500.2, U500.6 (VDD)
AUD_AMP_BYPASS: C508.2, U500.2 (BYPASS)
AUD_AMP_IN+: R505.1, R506.1, U500.3 (IN+)
AUD_AMP_IN+_FILTER: C507.2, R506.2
AUD_AMP_IN-: R503.2, R504.1, U500.4 (IN-)
AUD_AMP_VO+: LS500.+ (1), R504.2, U500.5 (VO+)
AUD_AMP_VO-: LS500.- (2), R505.2, U500.8 (VO-)
AUD_FILTER_S1: C503.1, R500.2, R501.1
AUD_FILTER_S2: C504.1, R501.2, R502.1
AUD_FILTER_S3: C505.1, C506.1, R502.2
AUD_FILTER_S4: C506.2, R503.1
AUD_GND: C500.2 (-), C501.2, C502.2, C503.2, C504.2, C505.2, C507.1, C508.1, C509.1, FB501.2, R507.2, U500.7 (GND), U500.TP1 (GND), U500.TP2 (GND)
GND: FB501.1, LS500.S1, LS500.S2; also elsewhere on the board

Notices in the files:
main.brd:
© 2018 Blockworker
